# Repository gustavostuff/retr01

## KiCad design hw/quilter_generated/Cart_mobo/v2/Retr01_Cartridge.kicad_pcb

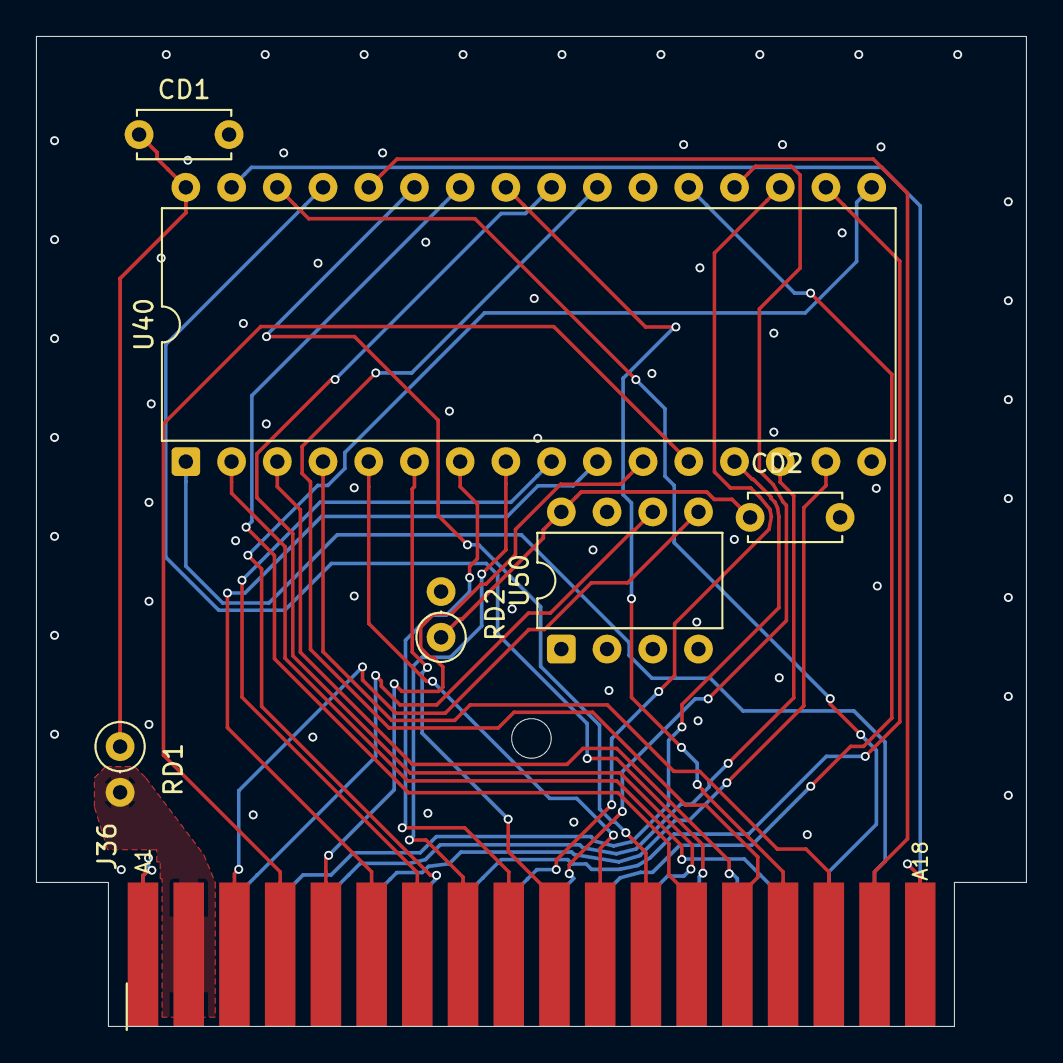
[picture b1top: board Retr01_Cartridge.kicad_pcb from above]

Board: 4 copper layers, 55.0 x 55.0 mm, 8 parts (0 on the bottom side), 35 nets.

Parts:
CD1, CD2: 100nF; C_Disc_D5.0mm_W2.5mm_P5.00mm
J36: CART_EDGE_36; Cart_Edge_2x18_P2.54mm
RD1, RD2: 0; R_Axial_DIN0207_L6.3mm_D2.5mm_P2.54mm_Vertical
Screw: MountingHole_2.2mm_M2
U40: SST39SF040; DIP-32_W15.24mm
U50: 24C64; DIP-8_W7.62mm

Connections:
+5V: J36.2, J36.20, RD1.2, RD2.2
+5V_U40: CD1.1, RD1.1, U40.32
+5V_U50: CD2.1, RD2.1, U50.8
CART_A0: J36.4, U40.12
CART_A1: J36.5, U40.11
CART_A2: J36.6, U40.10
CART_A3: J36.7, U40.9
CART_A4: J36.8, U40.8
CART_A5: J36.9, U40.7
CART_A6: J36.10, U40.6
CART_A7: J36.11, U40.5
CART_A8: J36.12, U40.27
CART_A9: J36.13, U40.26
CART_A10: J36.14, U40.23
CART_A11: J36.15, U40.25
CART_A12: J36.16, U40.4
CART_A13: J36.17, U40.28
CART_A14: J36.31, U40.29
CART_A15: J36.32, U40.3
CART_A16: J36.33, U40.2
CART_A17: J36.34, U40.30
CART_A18: J36.35, U40.1
CART_D0: J36.22, U40.13
CART_D1: J36.23, U40.14
CART_D2: J36.24, U40.15
CART_D3: J36.25, U40.17
CART_D4: J36.26, U40.18
CART_D5: J36.27, U40.19
CART_D6: J36.28, U40.20
CART_D7: J36.29, U40.21
CART_OE_N: J36.30, U40.24
CART_WE_N: J36.36, U40.31
GND: CD1.2, CD2.2, J36.1, J36.18, J36.19, U40.16, U40.22, U50.1, U50.2, U50.3, U50.4, U50.7
I2C_SCL: J36.21, U50.6
I2C_SDA: J36.3, U50.5

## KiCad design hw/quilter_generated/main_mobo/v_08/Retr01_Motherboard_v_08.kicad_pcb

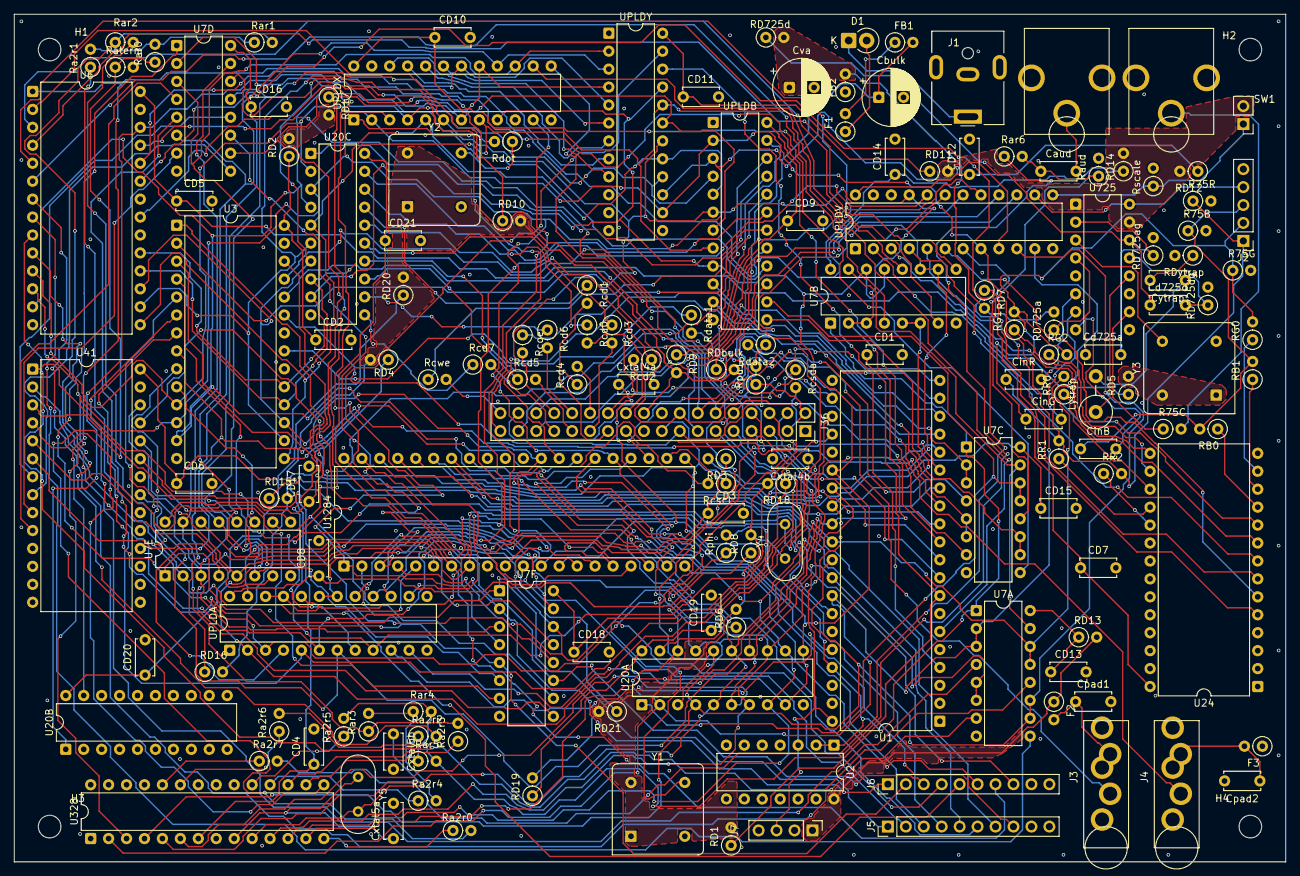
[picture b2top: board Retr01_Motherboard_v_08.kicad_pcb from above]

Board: 4 copper layers, 180.0 x 120.0 mm, 160 parts (0 on the bottom side), 214 nets.

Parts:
CD1, CD2, CD3, CD4, CD5, CD6, CD7, CD8, CD9, CD10, CD11, CD12, CD13, CD14, CD15, CD16, CD17, CD18, CD19, CD20, CD21: 100nF; C_Disc_D5.0mm_W2.5mm_P5.00mm
Caud: 10uF; C_Disc_D5.0mm_W2.5mm_P5.00mm
Cbulk: 220uF; CP_Radial_D8.0mm_P3.50mm
Cd725a, Cd725d: 100nF; C_Disc_D5.0mm_W2.5mm_P5.00mm
CinB: 100nF; C_Disc_D5.0mm_W2.5mm_P5.00mm
CinG: 100nF; C_Disc_D5.0mm_W2.5mm_P5.00mm
CinR: 100nF; C_Disc_D5.0mm_W2.5mm_P5.00mm
Cpad1, Cpad2: 100nF; C_Disc_D5.0mm_W2.5mm_P5.00mm
Cva: 10uF; CP_Radial_D8.0mm_P3.50mm
Cxtal4a, Cxtal4b, Cxtal5a, Cxtal5b: 22pF; C_Disc_D5.0mm_W2.5mm_P5.00mm
Cytrap: 100nF; C_Disc_D5.0mm_W2.5mm_P5.00mm
D1: SCHOTTKY; D_DO-41_SOD81_P2.54mm_Vertical_CathodeUp
F1, F2, F3: PPTC; R_Axial_DIN0207_L6.3mm_D2.5mm_P2.54mm_Vertical
FB1, FB2: FERRITE; R_Axial_DIN0207_L6.3mm_D2.5mm_P2.54mm_Vertical
H1, H2, H3, H4: MountingHole_3.2mm_M3
J1: BARREL_5V; BarrelJack_CUI_PJ-063AH_Horizontal
J2: RGBS_HDR; PinHeader_1x05_P2.54mm_Vertical
J3: TRS_P1; Jack_3.5mm_Switchcraft_35RAPC2BVN4_Vertical
J4: TRS_P2; Jack_3.5mm_Switchcraft_35RAPC2BVN4_Vertical
J5: ARCADE_P1; PinHeader_1x10_P2.54mm_Vertical
J6: ARCADE_P2; PinHeader_1x10_P2.54mm_Vertical
J7: CAB_PWR_RST; PinHeader_1x04_P2.54mm_Vertical
J8: AUDIO_OUT; CUI_RCJ-01x_Vertical
J9: COMPOSITE; CUI_RCJ-01x_Vertical
J36: CART_EDGE_36; PinSocket_2x18_P2.54mm_Vertical
Lytrap: L_YTRAP; L_Axial_L11.0mm_D4.5mm_P5.08mm_Vertical_Fastron_MECC
R75B, R75C, R75G, R75R: 75R; R_Axial_DIN0207_L6.3mm_D2.5mm_P2.54mm_Vertical
RB0: 2k; R_Axial_DIN0207_L6.3mm_D2.5mm_P2.54mm_Vertical
RB1: 1k; R_Axial_DIN0207_L6.3mm_D2.5mm_P2.54mm_Vertical
RD1, RD2, RD3, RD4, RD5, RD6, RD7, RD8, RD9, RD10, RD11, RD12, RD13, RD14, RD15, RD16, RD17, RD18, RD19, RD20, RD21: 0; R_Axial_DIN0207_L6.3mm_D2.5mm_P2.54mm_Vertical
RD725a, RD725ag, RD725d, RD725dg: 0R; R_Axial_DIN0207_L6.3mm_D2.5mm_P2.54mm_Vertical
RDbulk: 0R; R_Axial_DIN0207_L6.3mm_D2.5mm_P2.54mm_Vertical
RDytrap: 0R; R_Axial_DIN0207_L6.3mm_D2.5mm_P2.54mm_Vertical
RG0: 4k; R_Axial_DIN0207_L6.3mm_D2.5mm_P2.54mm_Vertical
RG1: 2k; R_Axial_DIN0207_L6.3mm_D2.5mm_P2.54mm_Vertical
RG2: 1k; R_Axial_DIN0207_L6.3mm_D2.5mm_P2.54mm_Vertical
RR0: 4k; R_Axial_DIN0207_L6.3mm_D2.5mm_P2.54mm_Vertical
RR1: 2k; R_Axial_DIN0207_L6.3mm_D2.5mm_P2.54mm_Vertical
RR2: 1k; R_Axial_DIN0207_L6.3mm_D2.5mm_P2.54mm_Vertical
Ra2r0, Ra2r1, Ra2r2, Ra2r3, Ra2r4, Ra2r5, Ra2r6, Ra2r7: 20k; R_Axial_DIN0207_L6.3mm_D2.5mm_P2.54mm_Vertical
Rar0, Rar1, Rar2, Rar3, Rar4, Rar5, Rar6: 10k; R_Axial_DIN0207_L6.3mm_D2.5mm_P2.54mm_Vertical
Raterm: 20k; R_Axial_DIN0207_L6.3mm_D2.5mm_P2.54mm_Vertical
Raud: 1k; R_Axial_DIN0207_L6.3mm_D2.5mm_P2.54mm_Vertical
Rcd0, Rcd1, Rcd2, Rcd3, Rcd4, Rcd5, Rcd6, Rcd7: 33R; R_Axial_DIN0207_L6.3mm_D2.5mm_P2.54mm_Vertical
Rcoe: 33R; R_Axial_DIN0207_L6.3mm_D2.5mm_P2.54mm_Vertical
Rcscl: 33R; R_Axial_DIN0207_L6.3mm_D2.5mm_P2.54mm_Vertical
Rcsda: 33R; R_Axial_DIN0207_L6.3mm_D2.5mm_P2.54mm_Vertical
Rcwe: 33R; R_Axial_DIN0207_L6.3mm_D2.5mm_P2.54mm_Vertical
Rdata1, Rdata2: 47R; R_Axial_DIN0207_L6.3mm_D2.5mm_P2.54mm_Vertical
Rdot: 33R; R_Axial_DIN0207_L6.3mm_D2.5mm_P2.54mm_Vertical
Rphi: 33R; R_Axial_DIN0207_L6.3mm_D2.5mm_P2.54mm_Vertical
Rpu1: 4.7k; R_Axial_DIN0207_L6.3mm_D2.5mm_P2.54mm_Vertical
Rscale: 10k; R_Axial_DIN0207_L6.3mm_D2.5mm_P2.54mm_Vertical
SW1: SCALE_SW; PinHeader_1x02_P2.54mm_Vertical
U1: W65C02S; DIP-40_W15.24mm
U2: SN74HC14; DIP-14_W7.62mm
U3, U6, U41: AS6C62256; DIP-28_W15.24mm
U7A, U7B, U7C, U7D, U7E, U7F: SN74HC157; DIP-16_W7.62mm
U20A, U20B, U20C: SN74HC245; DIP-20_W7.62mm
U24: AT27C256R; DIP-28_W15.24mm
U328: ATmega328P; DIP-28_W7.62mm
U725: AD725; DIP-16_W7.62mm
U1284: ATmega1284P; DIP-40_W15.24mm
UPLDA: ATF22V10; DIP-24_W7.62mm
UPLDB: ATF22V10; DIP-24_W7.62mm
UPLDV: ATF22V10; DIP-24_W7.62mm
UPLDX: ATF22V10; DIP-24_W7.62mm
UPLDY: ATF22V10; DIP-24_W7.62mm
Y1: OSC8M; Oscillator_DIP-8
Y2: OSC_DOT; Oscillator_DIP-8
Y3: OSC_4FSC; Oscillator_DIP-8
Y4: XTAL_20M; Crystal_HC49-U_Vertical
Y5: XTAL_16M; Crystal_HC49-U_Vertical

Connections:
+5V: F2.1, F3.1, FB2.1, J7.1, J36.2, J36.20, RD1.2, RD2.2, RD3.2, RD4.2, RD5.2, RD6.2, RD8.2, RD9.2, RD10.2, RD11.2, RD12.2, RD13.2, RD14.2, RD15.2, RD16.2, RD17.2, RD18.2, RD19.2, RD20.2, RD21.2, RDbulk.2, Rpu1.1, SW1.2, U2.14, U725.1, U725.5, U725.15, Y1.1, Y1.8, Y2.1, Y2.8, Y3.1, Y3.8
+5V_ANALOG: Cva.1, FB2.2, RD7.2, RD725a.2, RD725d.2
+5V_BULK: Cbulk.1, FB1.2, RDbulk.1
+5V_U1: CD1.1, RD1.1, U1.8
+5V_U3: CD2.1, RD2.1, U3.28
+5V_U6: CD5.1, RD5.1, U6.28
+5V_U7A: CD13.1, RD13.1, U7A.16
+5V_U7B: CD14.1, RD14.1, U7B.16
+5V_U7C: CD15.1, RD15.1, U7C.16
+5V_U7D: CD16.1, RD16.1, U7D.16
+5V_U7E: CD17.1, RD17.1, U7E.16
+5V_U7F: CD18.1, RD18.1, U7F.16
+5V_U20A: CD19.1, RD19.1, U20A.20
+5V_U20B: CD20.1, RD20.1, U20B.20
+5V_U20C: CD21.1, RD21.1, U20C.20
+5V_U24: CD7.1, RD7.1, U24.28
+5V_U41: CD6.1, RD6.1, U41.28
+5V_U328: CD4.1, RD4.1, U328.7
+5V_U725_APOS: Cd725a.1, RD725a.1, U725.4
+5V_U725_DPOS: Cd725d.1, RD725d.1, U725.14
+5V_U1284: CD3.1, RD3.1, U1284.10
+5V_UPLDA: CD8.1, RD8.1, UPLDA.24
+5V_UPLDB: CD9.1, RD9.1, UPLDB.24
+5V_UPLDV: CD12.1, RD12.1, UPLDV.24
+5V_UPLDX: CD10.1, RD10.1, UPLDX.24
+5V_UPLDY: CD11.1, RD11.1, UPLDY.24
AD725_BIN: CinB.2, U725.8
AD725_GIN: CinG.2, U725.7
AD725_RIN: CinR.2, U725.6
ASUM0: Ra2r0.2, Rar0.1, Raterm.1
ASUM1: Ra2r1.2, Rar0.2, Rar1.1
ASUM2: Ra2r2.2, Rar1.2, Rar2.1
ASUM3: Ra2r3.2, Rar2.2, Rar3.1
ASUM4: Ra2r4.2, Rar3.2, Rar4.1
ASUM5: Ra2r5.2, Rar4.2, Rar5.1
ASUM6: Ra2r6.2, Rar5.2, Rar6.1
AUD0: Ra2r0.1, U328.14
AUD1: Ra2r1.1, U328.15
AUD2: Ra2r2.1, U328.16
AUD3: Ra2r3.1, U328.17
AUD4: Ra2r4.1, U328.18
AUD5: Ra2r5.1, U328.19
AUD6: Ra2r6.1, U328.23
AUD7: Ra2r7.1, U328.24
AUDIO_OUT: Caud.2, J8.1
AUDIO_SUM: Caud.1, Ra2r7.2, Rar6.2, Raud.1
BEAM_LB_A5: U7D.6, U7E.6, U7F.6, UPLDX.16, UPLDY.3
BEAM_Y0: U7D.3, U7E.3, U7F.3, UPLDX.15, UPLDY.2
BEAM_Y2: U7D.10, U7E.10, U7F.10, UPLDX.17, UPLDY.4
BEAM_Y3: U7D.13, U7E.13, U7F.13, UPLDX.18, UPLDY.5
BEAM_Y4: UPLDX.19, UPLDY.6
BEAM_Y5: UPLDX.20, UPLDY.7
BEAM_Y6: UPLDX.21, UPLDY.8
BEAM_Y7: UPLDX.22, UPLDY.9
CART_A0: J36.4, U1.9, U3.10, UPLDA.2
CART_A1: J36.5, U1.10, U3.9, UPLDA.3
CART_A2: J36.6, U1.11, U3.8, UPLDA.4
CART_A7: J36.11, U1.16, U3.3, UPLDA.9
CART_A8: J36.12, U1.17, U3.25
CART_A9: J36.13, U1.18, U3.24
CART_A10: J36.14, U1.19, U3.21
CART_A14: J36.31, UPLDV.15
CART_A15: J36.32, UPLDV.16
CART_A16: J36.33, UPLDV.17
CART_A17: J36.34, UPLDV.18
CART_A18: J36.35, UPLDV.19
CART_D0: J36.22, Rcd0.2
CART_D0_MCU: Rcd0.1, U20C.18
CART_D1: J36.23, Rcd1.2
CART_D1_MCU: Rcd1.1, U20C.17
CART_D2: J36.24, Rcd2.2
CART_D2_MCU: Rcd2.1, U20C.16
CART_D3: J36.25, Rcd3.2
CART_D3_MCU: Rcd3.1, U20C.15
CART_D4: J36.26, Rcd4.2
CART_D4_MCU: Rcd4.1, U20C.14
CART_D5: J36.27, Rcd5.2
CART_D5_MCU: Rcd5.1, U20C.13
CART_D6: J36.28, Rcd6.2
CART_D6_MCU: Rcd6.1, U20C.12
CART_D7: J36.29, Rcd7.2
CART_D7_MCU: Rcd7.1, U20C.11
CART_OE_MCU: Rcoe.1, UPLDB.20
CART_OE_N: J36.30, Rcoe.2
CART_WE_MCU: Rcwe.1, UPLDB.21
CART_WE_N: J36.36, Rcwe.2
COMPOSITE_OUT: J9.1, R75C.2
COMP_RAW: R75C.1, U725.10
CPU_A3: J36.7, U1.12, U3.7, UPLDA.5
CPU_A4: J36.8, U1.13, U3.6, UPLDA.6
CPU_A5: J36.9, U1.14, U3.5, UPLDA.7
CPU_A11: J36.15, U1.20, U3.23
CPU_A12: J36.16, U1.22, U3.2
CPU_A13: J36.17, U1.23, U3.26
CPU_A14: U1.24, U3.1
CPU_A_LO6: J36.10, U1.15, U3.4, UPLDA.8
CPU_BE: U1.36, UPLDA.10
CPU_D3: U1.30, U3.15, U6.15, U7A.13, U7A.14, U20A.5, U20A.15, U20C.5, U328.5, U1284.27, UPLDB.5, UPLDV.11, UPLDX.5, UPLDY.17
CPU_D5: U1.28, U3.17, U6.17, U7B.5, U7B.6, U20A.7, U20A.13, U20C.7, U328.11, U1284.29, UPLDB.7, UPLDX.7, UPLDY.19
CPU_D6: U1.27, U3.18, U6.18, U7B.10, U7B.11, U20A.8, U20A.12, U20C.8, U328.12, U1284.20, UPLDB.8, UPLDX.8, UPLDY.20
CPU_RWB: U1.34, UPLDA.11
CPU_VA0: U1.33, U3.11, U6.11, U7A.2, U7A.3, U20A.2, U20A.18, U20C.2, U328.2, U1284.24, UPLDB.2, UPLDV.8, UPLDX.2, UPLDY.14
CPU_VA2: U1.31, U3.13, U6.13, U7A.10, U7A.11, U20A.4, U20A.16, U20C.4, U328.4, U1284.26, UPLDB.4, UPLDV.10, UPLDX.4, UPLDY.16
CPU_VA4: U1.29, U3.16, U6.16, U7B.2, U7B.3, U20A.6, U20A.14, U20C.6, U328.6, U1284.28, UPLDB.6, UPLDV.21, UPLDX.6, UPLDY.18
CPU_VA10: U7C.10, U7C.11, UPLDB.13
CPU_VA11: U7C.13, U7C.14, U20A.1, UPLDB.14
CSYNC: J2.4, U725.16, UPLDV.14
DIR_CART245: U20C.1, UPLDB.18
DIR_VID245: U6.26, U20B.1, UPLDB.16
DOT_CLK: Rdot.2, UPLDX.1
DOT_SRC: Rdot.1, Y2.5
FSC4: U725.3, Y3.5
GND: CD1.2, CD2.2, CD3.2, CD4.2, CD5.2, CD6.2, CD7.2, CD8.2, CD9.2, CD10.2, CD11.2, CD12.2, CD13.2, CD14.2, CD15.2, CD16.2, CD17.2, CD18.2, CD19.2, CD20.2, CD21.2, Cbulk.2, Cpad1.2, Cpad2.2, Cva.2, Cxtal4a.2, Cxtal4b.2, Cxtal5a.2, Cxtal5b.2, J1.2, J1.MP, J2.5, J3.1, J4.1, J5.9, J5.10, J6.9, J6.10, J7.2, J7.4, J8.2, J9.2, J36.1, J36.18, J36.19, R75B.2, R75G.2, R75R.2, RD725ag.2, RD725dg.2, RDytrap.2, Raterm.2, Rscale.2, U1.21, U3.14, U6.14, U7A.8, U7B.8, U7C.8, U7D.8, U7E.8, U7F.8, U20A.10, U20B.10, U20C.10, U24.14, U41.14, U328.8, U1284.11, UPLDA.12, UPLDB.12, UPLDV.12, UPLDX.12, UPLDY.12, Y1.4, Y2.4, Y3.4
GND_U725_AGND: Cd725a.2, RD725ag.1, U725.2
GND_U725_DGND: Cd725d.2, RD725dg.1, U725.13
I2C_SCL: J36.21, Rcscl.2
I2C_SCL_MCU: Rcscl.1, U1284.22
I2C_SDA: J36.3, Rcsda.2
I2C_SDA_MCU: Rcsda.1, U1284.23
IRQ_N: U1.4, UPLDY.22
LB_A0: U7D.4, U41.10
LB_A1: U7D.7, U41.9
LB_A2: U7D.9, U41.8
LB_A3: U7D.12, U41.7
LB_A4: U7E.4, U41.6
LB_A5: U7E.7, U41.5
LB_A6: U7E.9, U41.4
LB_A7: U7E.12, U41.3
LB_A8: U7F.4, U41.25
LB_A9: U7F.7, U41.24
LB_A10: U7F.9, U41.21
LB_A11: U7F.12, U41.23
LB_MUX_AB: U7D.1, U7E.1, U7F.1, U1284.17
LB_MUX_G_N: U7D.15, U7E.15, U7F.15
MCU_LB_A2: J6.3, U7D.11, U7F.11, U1284.3
MCU_LB_A3: J6.4, U7D.14, U7F.14, U1284.4
MCU_LB_A4: J6.5, U7E.2, U41.2, U1284.5
MCU_LB_A6: J6.7, U7E.11, U41.1, U1284.7
MCU_LB_A7: J6.8, U7E.14, U1284.8
MUX_G_N: U7A.15, U7B.15, U7C.15
NMI_N: U1.6, UPLDX.14
OE_CART245: U20C.19, UPLDB.19
P1_COIN: J5.7, U1284.34
P1_DOWN: J5.3, U1284.38
P1_LEFT: J5.2, U1284.39
P1_RIGHT: J5.1, U1284.40
P1_START: J5.8, U1284.33
P1_UP: J5.4, U1284.37
P1_X: J5.5, U1284.36
P1_Y: J5.6, U1284.35
P2_LEFT: J6.2, U7D.5, U7F.5, U1284.2
P2_RIGHT: J6.1, U7D.2, U7F.2, U1284.1
P2_Y: J6.6, U7E.5, U41.26, U1284.6
PAD_DATA: Rdata1.1, Rdata2.1, Rpu1.2, U1284.16
PAD_DATA_P1: J3.2, Rdata1.2
PAD_DATA_P2: J4.2, Rdata2.2
PAD_VCC_P1: Cpad1.1, F2.2, J3.4
PAD_VCC_P2: Cpad2.1, F3.2, J4.4
PHI2_BUF: Rphi.2, U1.37, U2.1, U2.2, U7A.1, U7B.1, U7C.1
PHI2_SRC: Rphi.1, Y1.5
PPU_VA1: U1.32, U3.12, U6.12, U7A.5, U7A.6, U20A.3, U20A.17, U20C.3, U328.3, U1284.25, UPLDB.3, UPLDV.9, UPLDX.3, UPLDY.15
PPU_VA7: U1.26, U3.19, U6.19, U7B.13, U7B.14, U20A.9, U20A.11, U20C.9, U328.13, U1284.21, UPLDB.9, UPLDX.9, UPLDY.21
PPU_VA8: U7C.2, U7C.3, UPLDB.10
PPU_VA9: U7C.5, U7C.6, UPLDB.11
PROM_A0: U24.10, UPLDV.2
PROM_A1: U24.9, UPLDV.3
PROM_A2: U24.8, UPLDV.4
PROM_A3: U24.7, UPLDV.5
PROM_A4: U24.6, UPLDV.6
PROM_A5: U24.5, UPLDV.7
PROM_D0: RB0.1, U24.11
PROM_D1: RB1.1, U24.12
PROM_D2: RG0.1, U24.13
PROM_D3: RG1.1, U24.15
PROM_D4: RG2.1, U24.16
PROM_D5: RR0.1, U24.17
PROM_D6: RR1.1, U24.18
PROM_D7: RR2.1, U24.19
RESET_N: J7.3, U1.40, U2.3, UPLDX.13
SCALE_1X: Rscale.1, SW1.1, UPLDV.13
SEL_FE02: U1284.19, UPLDA.15, UPLDB.23
SEL_FE03: UPLDA.16, UPLDX.11
SEL_FE04: UPLDA.17, UPLDY.23
SEL_FE05: U1284.14, UPLDA.18, UPLDA.19
SEL_FE06: U1284.18, UPLDA.14
SEL_FE10: UPLDA.23, UPLDB.22
SEL_FE92: U1284.15, UPLDA.20, UPLDA.21, UPLDA.22, UPLDV.20
VIDEO_B: CinB.1, J2.3, R75B.1, RB0.2, RB1.2
VIDEO_G: CinG.1, J2.2, R75G.1, RG0.2, RG1.2, RG2.2
VIDEO_R: CinR.1, J2.1, R75R.1, RR0.2, RR1.2, RR2.2
VIN_FUSED: F1.2, FB1.1
VIN_PROT: D1.2, F1.1
VIN_RAW: D1.1, J1.1
VRAM_A0: U6.10, U7A.4
VRAM_A1: U6.9, U7A.7
VRAM_A2: U6.8, U7A.9
VRAM_A3: U6.7, U7A.12
VRAM_A4: U6.6, U7B.4
VRAM_A5: U6.5, U7B.7
VRAM_A6: U6.4, U7B.9
VRAM_A7: U6.3, U7B.12
VRAM_A8: U6.25, U7C.4
VRAM_A9: U6.24, U7C.7
VRAM_A10: U6.21, U7C.9
VRAM_A11: U6.23, U7C.12
VRAM_A12: U6.2, U20A.19, UPLDB.15
VRAM_A14: U6.1, U20B.19, UPLDB.17
XTAL328: Cxtal5a.1, U328.9, Y5.1
XTAL328b: Cxtal5b.1, U328.10, Y5.2
XTAL1284: Cxtal4a.1, U1284.13, Y4.1
XTAL1284b: Cxtal4b.1, U1284.12, Y4.2
YTRAP: Lytrap.1, U725.12
YTRAP_MID: Cytrap.1, Lytrap.2
YTRAP_RET: Cytrap.2, RDytrap.1
